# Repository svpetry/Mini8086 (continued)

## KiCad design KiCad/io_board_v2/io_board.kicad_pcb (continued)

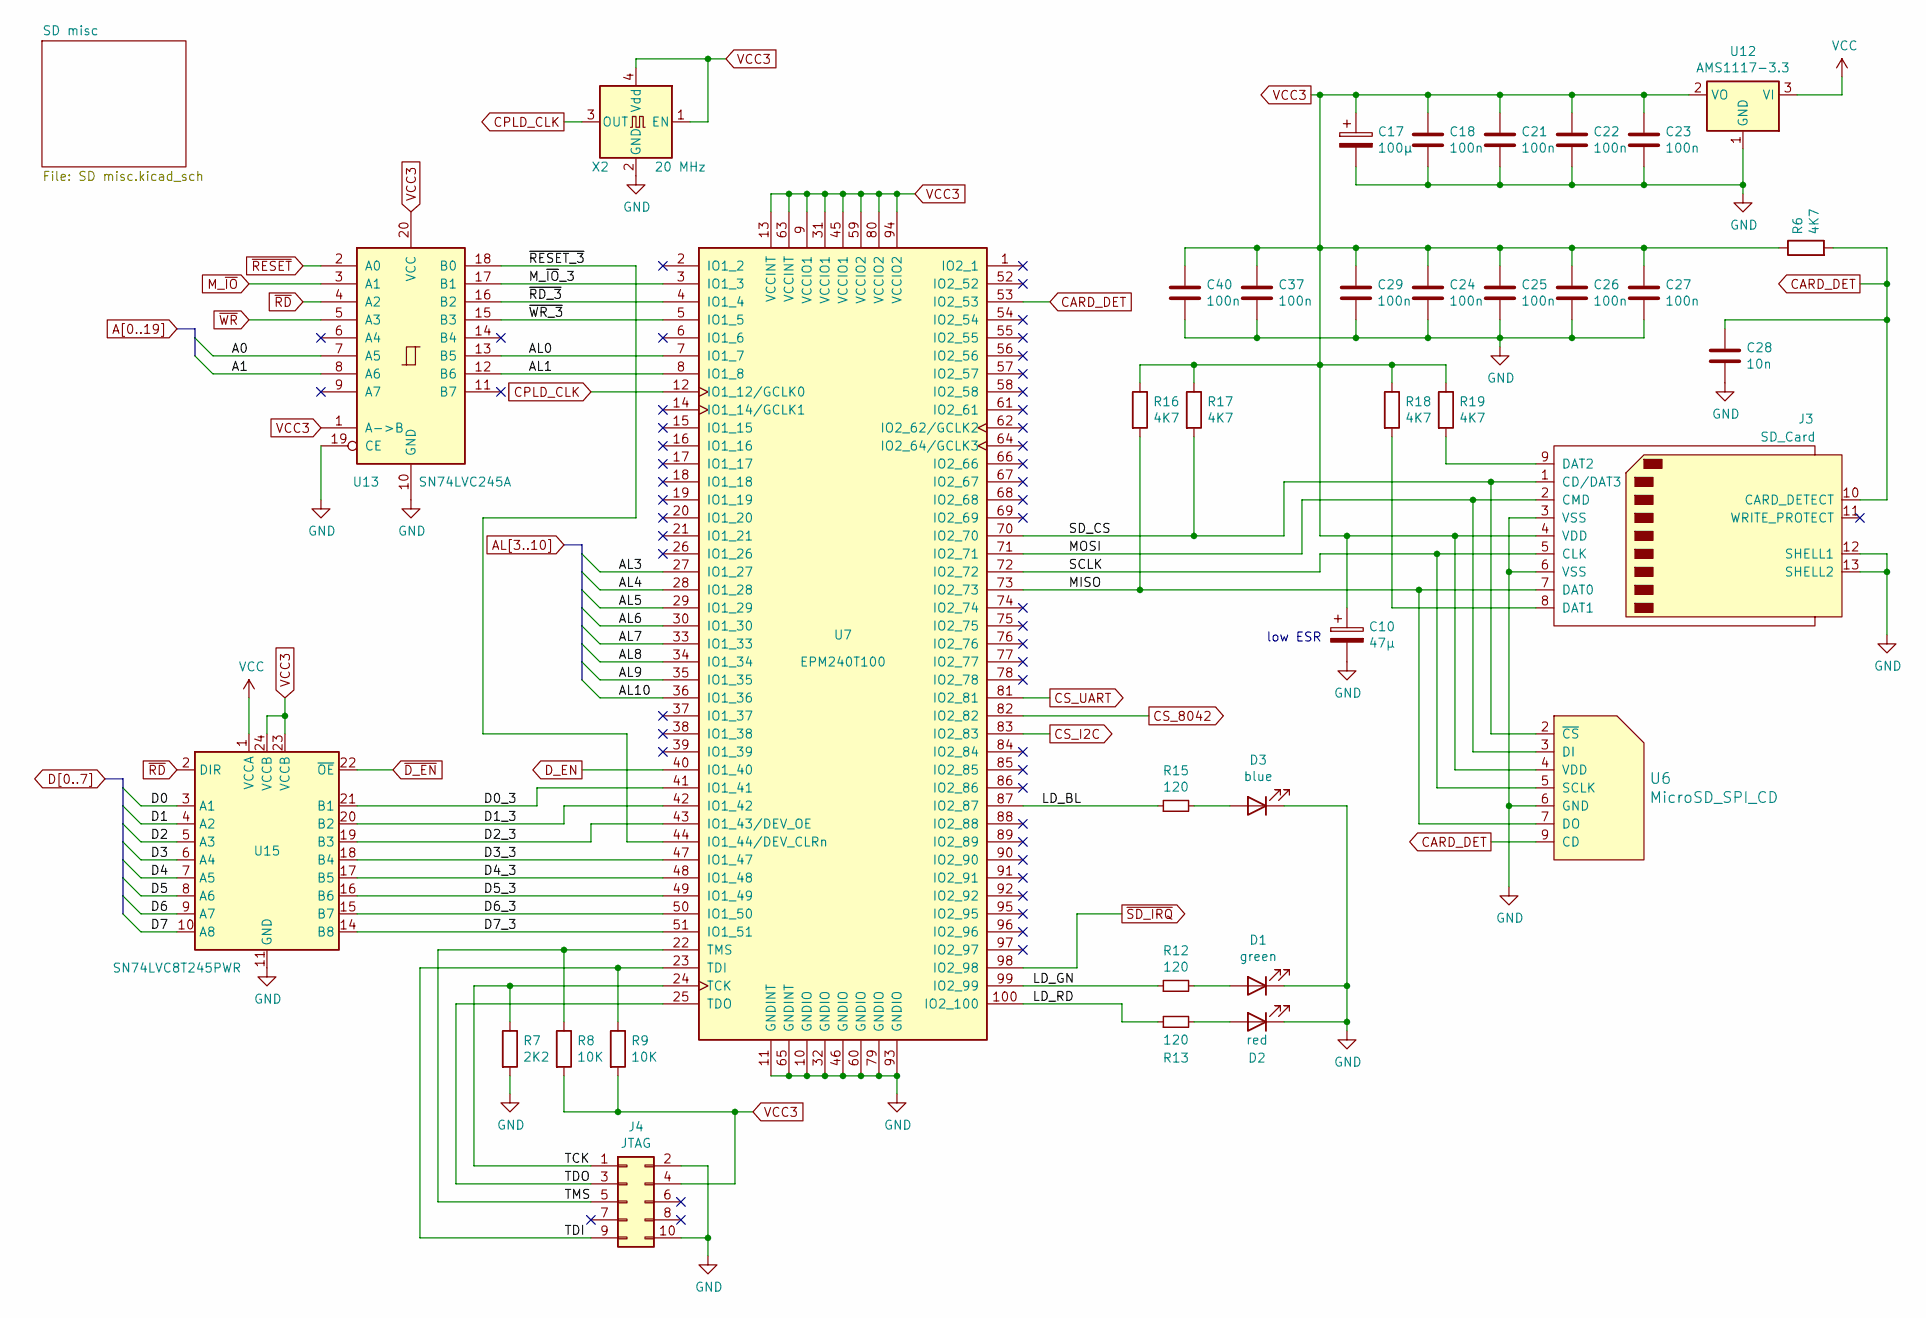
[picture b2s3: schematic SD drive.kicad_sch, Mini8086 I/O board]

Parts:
C10: 47µ; CP_Elec_5x5.4
C17: 100µ; CP_Elec_5x5.4
C18, C22, C24, C25, C26, C29, C37, C40: 100n; C_1206_3216Metric
C21, C23, C27: 100n; C_0805_2012Metric
C28: 10n; C_1206_3216Metric
D1: green; LED_1206_3216Metric
D2: red; LED_1206_3216Metric
D3: blue; LED_1206_3216Metric
J3: SD_Card; SD_TE_2041021
J4: JTAG; IDC-Header_2x05_P2.54mm_Vertical
R6, R16, R17, R18, R19: 4K7; R_1206_3216Metric
R7: 2K2; R_1206_3216Metric
R8, R9: 10K; R_1206_3216Metric
R12, R13, R15: 120; R_1206_3216Metric
U6: MicroSD_SPI_CD; GCT-MEM2055-00-190-01-A
U7: EPM240T100; LQFP-100_14x14mm_P0.5mm
U12: AMS1117-3.3; SOT-223-3_TabPin2
U13: SN74LVC245A; TSSOP-20_4.4x6.5mm_P0.65mm
U15: SN74LVC8T245PWR; TSSOP-24_4.4x7.8mm_P0.65mm
X2: 20 MHz; Oscillator_SMD_Abracon_ASV-4Pin_7.0x5.1mm

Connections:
/SD drive/AL0: U7.7 (IO1_7), U13.13 (B5)
/SD drive/AL1: U7.8 (IO1_8), U13.12 (B6)
/SD drive/D0_3: U7.41 (IO1_41), U15.21 (B1)
/SD drive/D1_3: U7.42 (IO1_42), U15.20 (B2)
/SD drive/D2_3: U7.43 (IO1_43/DEV_OE), U15.19 (B3)
/SD drive/D3_3: U7.47 (IO1_47), U15.18 (B4)
/SD drive/D4_3: U7.48 (IO1_48), U15.17 (B5)
/SD drive/D5_3: U7.49 (IO1_49), U15.16 (B6)
/SD drive/D6_3: U7.50 (IO1_50), U15.15 (B7)
/SD drive/D7_3: U7.51 (IO1_51), U15.14 (B8)
/SD drive/LD_BL: R15.1, U7.87 (IO2_87)
/SD drive/LD_GN: R12.1, U7.99 (IO2_99)
/SD drive/LD_RD: R13.1, U7.100 (IO2_100)
/SD drive/MISO: J3.7 (DAT0), R16.2, U6.7 (DO), U7.73 (IO2_73)
/SD drive/MOSI: J3.2 (CMD), U6.3 (DI), U7.71 (IO2_71)
/SD drive/M_~IO_3: U7.3 (IO1_3), U13.17 (B1)
/SD drive/SCLK: J3.5 (CLK), U6.5 (SCLK), U7.72 (IO2_72)
/SD drive/SD_CS: J3.1 (CD/DAT3), R17.2, U6.2 (~CS), U7.70 (IO2_70)
/SD drive/TCK: J4.1, R7.1, U7.24 (TCK)
/SD drive/TDI: J4.9, R9.1, U7.23 (TDI)
/SD drive/TDO: J4.3, U7.25 (TDO)
/SD drive/TMS: J4.5, R8.1, U7.22 (TMS)
/SD drive/~RD_3: U7.4 (IO1_4), U13.16 (B2)
/SD drive/~RESET_3: U7.44 (IO1_44/DEV_CLRn), U13.18 (B0)
/SD drive/~WR_3: U7.5 (IO1_5), U13.15 (B3)
A0: U13.7 (A5); also elsewhere on the board
A1: U13.8 (A6); also elsewhere on the board
AL3: U7.27 (IO1_27); also elsewhere on the board
AL4: U7.28 (IO1_28); also elsewhere on the board
AL5: U7.29 (IO1_29); also elsewhere on the board
AL6: U7.30 (IO1_30); also elsewhere on the board
AL7: U7.33 (IO1_33); also elsewhere on the board
AL8: U7.34 (IO1_34); also elsewhere on the board
AL9: U7.35 (IO1_35); also elsewhere on the board
AL10: U7.36 (IO1_36); also elsewhere on the board
CARD_DET: C28.1, J3.10 (CARD_DETECT), R6.2, U6.9 (CD), U7.53 (IO2_53)
CPLD_CLK: U7.12 (IO1_12/GCLK0), X2.3 (OUT)
CS_8042: U7.82 (IO2_82); also elsewhere on the board
CS_I2C: U7.83 (IO2_83); also elsewhere on the board
CS_UART: U7.81 (IO2_81); also elsewhere on the board
D0: U15.3 (A1); also elsewhere on the board
D1: U15.4 (A2); also elsewhere on the board
D2: U15.5 (A3); also elsewhere on the board
D3: U15.6 (A4); also elsewhere on the board
D4: U15.7 (A5); also elsewhere on the board
D5: U15.8 (A6); also elsewhere on the board
D6: U15.9 (A7); also elsewhere on the board
D7: U15.10 (A8); also elsewhere on the board
D_EN: U7.40 (IO1_40); also elsewhere on the board
GND: C10.2, C17.2, C18.2, C21.2, C22.2, C23.2, C24.2, C25.2, C26.2, C27.2, C28.2, C29.2, C37.2, C40.2, D1.1 (K), D2.1 (K), D3.1 (K), J3.3 (VSS), J3.6 (VSS), J3.12 (SHELL1), J3.13 (SHELL2), J4.2, J4.10, R7.2, U6.6 (GND), U7.10 (GNDIO), U7.11 (GNDINT), U7.32 (GNDIO), U7.46 (GNDIO), U7.60 (GNDIO), U7.65 (GNDINT), U7.79 (GNDIO), U7.93 (GNDIO), U12.1 (GND), U13.10 (GND), U13.19 (CE), U15.11 (GND), U15.12 (GND), U15.13 (GND), X2.2 (GND); also elsewhere on the board
M_~IO: U13.3 (A1); also elsewhere on the board
unnamed: D1.2 (A), R12.2
unnamed: D2.2 (A), R13.2
unnamed: D3.2 (A), R15.2
unnamed: J3.8 (DAT1), R18.2
unnamed: J3.9 (DAT2), R19.2
VCC: U12.3 (VI), U15.1 (VCCA); also elsewhere on the board
VCC3: C10.1, C17.1, C18.1, C21.1, C22.1, C23.1, C24.1, C25.1, C26.1, C27.1, C29.1, C37.1, C40.1, J3.4 (VDD), J4.4, R6.1, R8.2, R9.2, R16.1, R17.1, R18.1, R19.1, U6.4 (VDD), U7.9 (VCCIO1), U7.13 (VCCINT), U7.31 (VCCIO1), U7.45 (VCCIO1), U7.59 (VCCIO2), U7.63 (VCCINT), U7.80 (VCCIO2), U7.94 (VCCIO2), U12.2 (VO), U13.1 (A->B), U13.20 (VCC), U15.23 (VCCB), U15.24 (VCCB), X2.1 (EN), X2.4 (Vdd); also elsewhere on the board
~D_EN: U15.22 (~OE); also elsewhere on the board
~RD: U13.4 (A2), U15.2 (DIR); also elsewhere on the board
~RESET: U13.2 (A0); also elsewhere on the board
~SD_IRQ: U7.98 (IO2_98); also elsewhere on the board
~WR: U13.5 (A3); also elsewhere on the board

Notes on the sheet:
low ESR

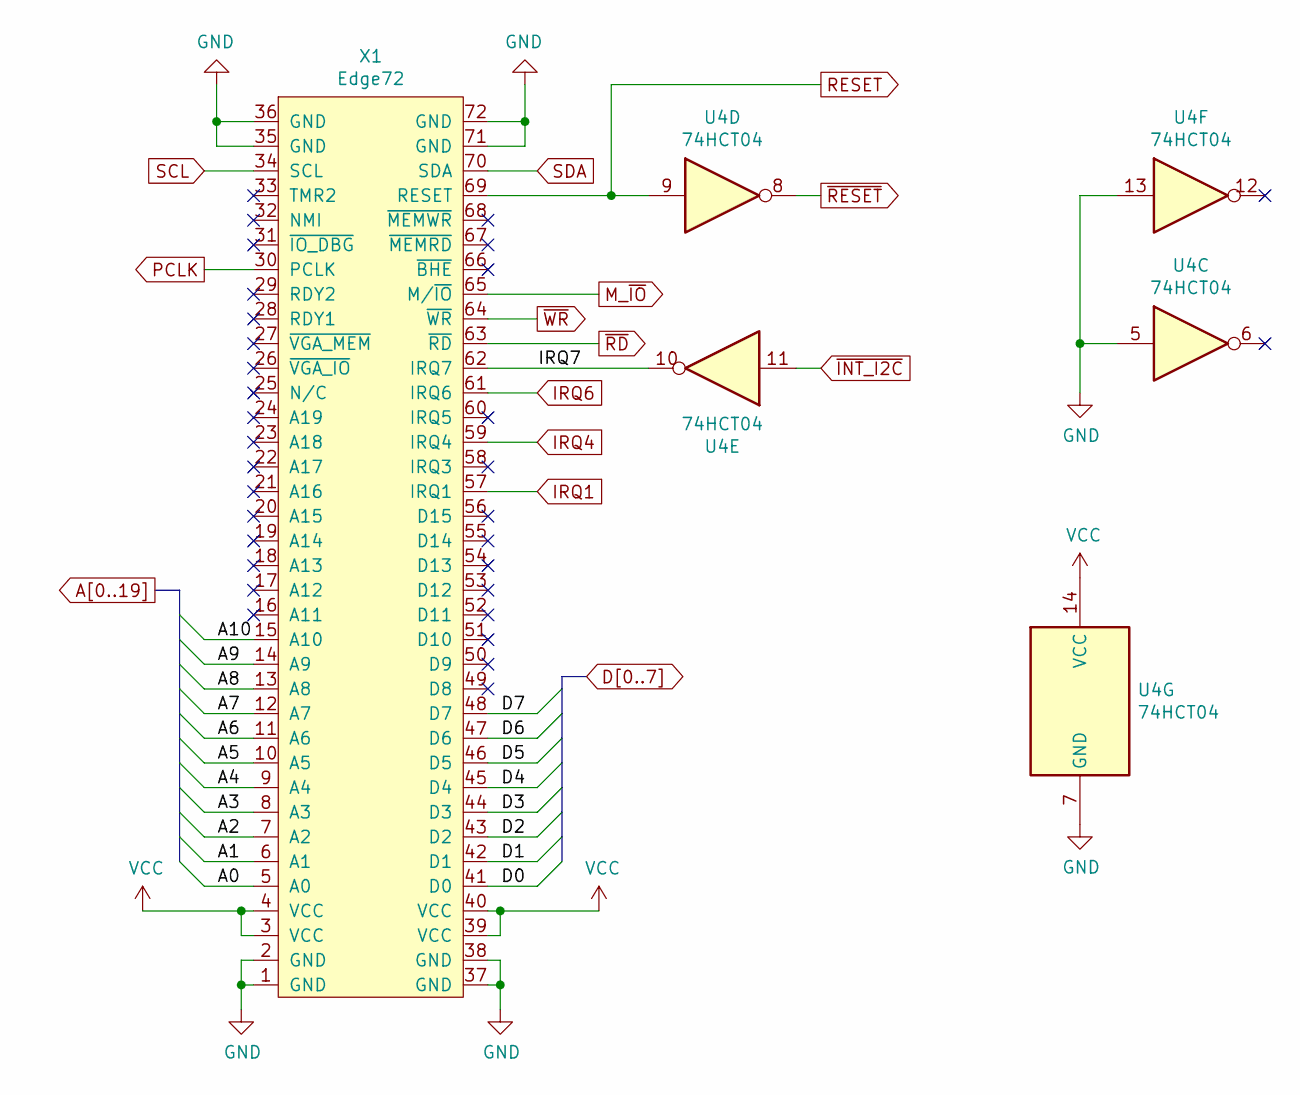
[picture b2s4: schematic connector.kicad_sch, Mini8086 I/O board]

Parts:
U4: 74HCT04; SOIC-14_3.9x8.7mm_P1.27mm
X1: Edge72; BUS_72

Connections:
/connector/IRQ7: U4.10, X1.62 (IRQ7)
A0: X1.5 (A0); also elsewhere on the board
A1: X1.6 (A1); also elsewhere on the board
A2: X1.7 (A2); also elsewhere on the board
A3: X1.8 (A3); also elsewhere on the board
A4: X1.9 (A4); also elsewhere on the board
A5: X1.10 (A5); also elsewhere on the board
A6: X1.11 (A6); also elsewhere on the board
A7: X1.12 (A7); also elsewhere on the board
A8: X1.13 (A8); also elsewhere on the board
A9: X1.14 (A9); also elsewhere on the board
A10: X1.15 (A10); also elsewhere on the board
D0: X1.41 (D0); also elsewhere on the board
D1: X1.42 (D1); also elsewhere on the board
D2: X1.43 (D2); also elsewhere on the board
D3: X1.44 (D3); also elsewhere on the board
D4: X1.45 (D4); also elsewhere on the board
D5: X1.46 (D5); also elsewhere on the board
D6: X1.47 (D6); also elsewhere on the board
D7: X1.48 (D7); also elsewhere on the board
GND: U4.5, U4.7 (GND), U4.13, X1.1 (GND), X1.2 (GND), X1.35 (GND), X1.36 (GND), X1.37 (GND), X1.38 (GND), X1.71 (GND), X1.72 (GND); also elsewhere on the board
IRQ1: X1.57 (IRQ1); also elsewhere on the board
IRQ4: X1.59 (IRQ4); also elsewhere on the board
IRQ6: X1.61 (IRQ6); also elsewhere on the board
M_~IO: X1.65 (M/~IO); also elsewhere on the board
PCLK: X1.30 (PCLK); also elsewhere on the board
RESET: U4.9, X1.69 (RESET); also elsewhere on the board
SCL: X1.34 (SCL); also elsewhere on the board
SDA: X1.70 (SDA); also elsewhere on the board
VCC: U4.14 (VCC), X1.3 (VCC), X1.4 (VCC), X1.39 (VCC), X1.40 (VCC); also elsewhere on the board
~INT_I2C: U4.11; also elsewhere on the board
~RD: X1.63 (~RD); also elsewhere on the board
~RESET: U4.8; also elsewhere on the board
~WR: X1.64 (~WR); also elsewhere on the board

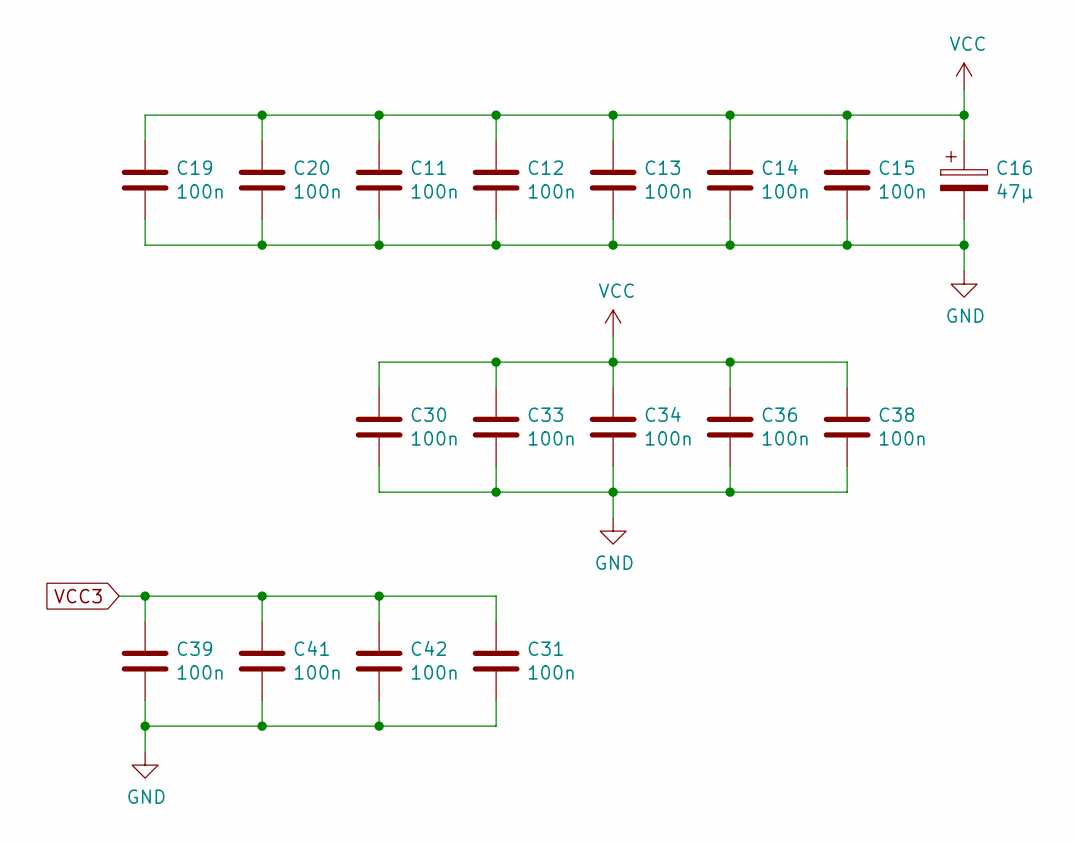
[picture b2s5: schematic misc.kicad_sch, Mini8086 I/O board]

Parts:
C11, C12, C13, C14, C15, C19, C20, C30, C33, C34, C36, C38, C39, C41, C42: 100n; C_1206_3216Metric
C16: 47µ; CP_Radial_D5.0mm_P2.00mm
C31: 100n; C_0805_2012Metric

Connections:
GND: C11.2, C12.2, C13.2, C14.2, C15.2, C16.2, C19.2, C20.2, C30.2, C31.2, C33.2, C34.2, C36.2, C38.2, C39.2, C41.2, C42.2; also elsewhere on the board
VCC: C11.1, C12.1, C13.1, C14.1, C15.1, C16.1, C19.1, C20.1, C30.1, C33.1, C34.1, C36.1, C38.1; also elsewhere on the board
VCC3: C31.1, C39.1, C41.1, C42.1; also elsewhere on the board

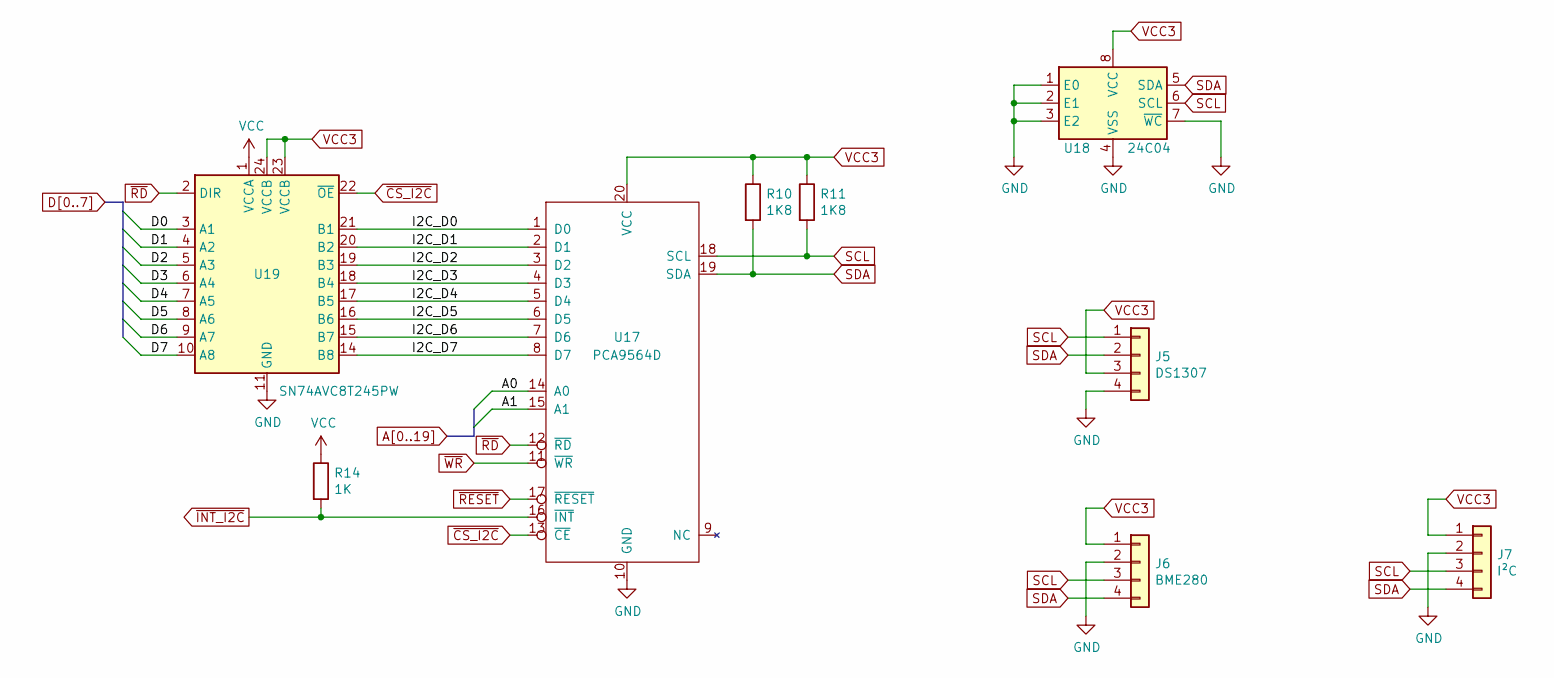
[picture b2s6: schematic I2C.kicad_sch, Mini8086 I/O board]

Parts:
J5: DS1307; PinHeader_1x04_P2.54mm_Vertical
J6: BME280; PinHeader_1x04_P2.54mm_Vertical
J7: I²C; PinHeader_1x04_P2.54mm_Vertical
R10, R11: 1K8; R_1206_3216Metric
R14: 1K; R_1206_3216Metric
U17: PCA9564D; SOIC-20W_7.5x12.8mm_P1.27mm
U18: 24C04; SOIC-8_3.9x4.9mm_P1.27mm
U19: SN74AVC8T245PW; TSSOP-24_4.4x7.8mm_P0.65mm

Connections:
/I2C/I2C_D0: U17.1 (D0), U19.21 (B1)
/I2C/I2C_D1: U17.2 (D1), U19.20 (B2)
/I2C/I2C_D2: U17.3 (D2), U19.19 (B3)
/I2C/I2C_D3: U17.4 (D3), U19.18 (B4)
/I2C/I2C_D4: U17.5 (D4), U19.17 (B5)
/I2C/I2C_D5: U17.6 (D5), U19.16 (B6)
/I2C/I2C_D6: U17.7 (D6), U19.15 (B7)
/I2C/I2C_D7: U17.8 (D7), U19.14 (B8)
A0: U17.14 (A0); also elsewhere on the board
A1: U17.15 (A1); also elsewhere on the board
D0: U19.3 (A1); also elsewhere on the board
D1: U19.4 (A2); also elsewhere on the board
D2: U19.5 (A3); also elsewhere on the board
D3: U19.6 (A4); also elsewhere on the board
D4: U19.7 (A5); also elsewhere on the board
D5: U19.8 (A6); also elsewhere on the board
D6: U19.9 (A7); also elsewhere on the board
D7: U19.10 (A8); also elsewhere on the board
GND: J5.4, J6.2, J7.2, U17.10 (GND), U18.1 (E0), U18.2 (E1), U18.3 (E2), U18.4 (VSS), U18.7 (~WC), U19.11 (GND), U19.12 (GND), U19.13 (GND); also elsewhere on the board
SCL: J5.1, J6.3, J7.3, R11.2, U17.18 (SCL), U18.6 (SCL); also elsewhere on the board
SDA: J5.2, J6.4, J7.4, R10.2, U17.19 (SDA), U18.5 (SDA); also elsewhere on the board
VCC: R14.1, U19.1 (VCCA); also elsewhere on the board
VCC3: J5.3, J6.1, J7.1, R10.1, R11.1, U17.20 (VCC), U18.8 (VCC), U19.23 (VCCB), U19.24 (VCCB); also elsewhere on the board
~CS_I2C: U17.13 (~CE), U19.22 (~OE); also elsewhere on the board
~INT_I2C: R14.2, U17.16 (~INT); also elsewhere on the board
~RD: U17.12 (~RD), U19.2 (DIR); also elsewhere on the board
~RESET: U17.17 (~RESET); also elsewhere on the board
~WR: U17.11 (~WR); also elsewhere on the board

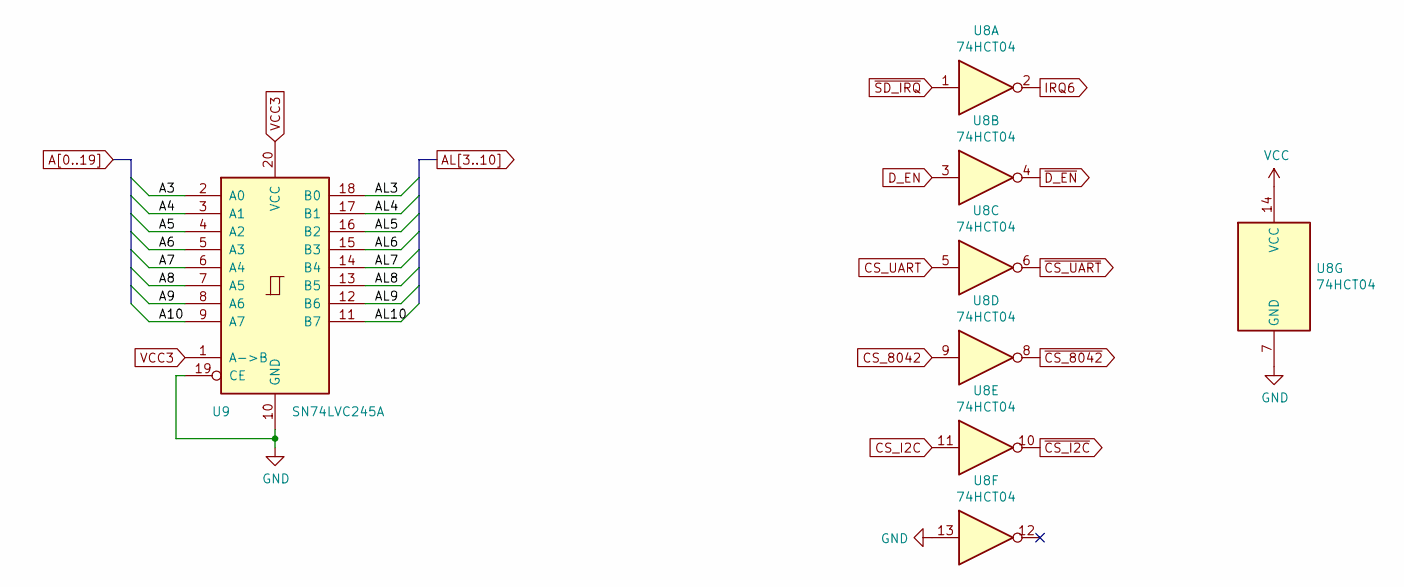
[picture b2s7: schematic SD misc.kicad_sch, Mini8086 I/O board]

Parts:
U8: 74HCT04; SOIC-14_3.9x8.7mm_P1.27mm
U9: SN74LVC245A; TSSOP-20_4.4x6.5mm_P0.65mm

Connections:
A3: U9.2 (A0); also elsewhere on the board
A4: U9.3 (A1); also elsewhere on the board
A5: U9.4 (A2); also elsewhere on the board
A6: U9.5 (A3); also elsewhere on the board
A7: U9.6 (A4); also elsewhere on the board
A8: U9.7 (A5); also elsewhere on the board
A9: U9.8 (A6); also elsewhere on the board
A10: U9.9 (A7); also elsewhere on the board
AL3: U9.18 (B0); also elsewhere on the board
AL4: U9.17 (B1); also elsewhere on the board
AL5: U9.16 (B2); also elsewhere on the board
AL6: U9.15 (B3); also elsewhere on the board
AL7: U9.14 (B4); also elsewhere on the board
AL8: U9.13 (B5); also elsewhere on the board
AL9: U9.12 (B6); also elsewhere on the board
AL10: U9.11 (B7); also elsewhere on the board
CS_8042: U8.9; also elsewhere on the board
CS_I2C: U8.11; also elsewhere on the board
CS_UART: U8.5; also elsewhere on the board
D_EN: U8.3; also elsewhere on the board
GND: U8.7 (GND), U8.13, U9.10 (GND), U9.19 (CE); also elsewhere on the board
IRQ6: U8.2; also elsewhere on the board
VCC: U8.14 (VCC); also elsewhere on the board
VCC3: U9.1 (A->B), U9.20 (VCC); also elsewhere on the board
~CS_8042: U8.8; also elsewhere on the board
~CS_I2C: U8.10; also elsewhere on the board
~CS_UART: U8.6; also elsewhere on the board
~D_EN: U8.4; also elsewhere on the board
~SD_IRQ: U8.1; also elsewhere on the board

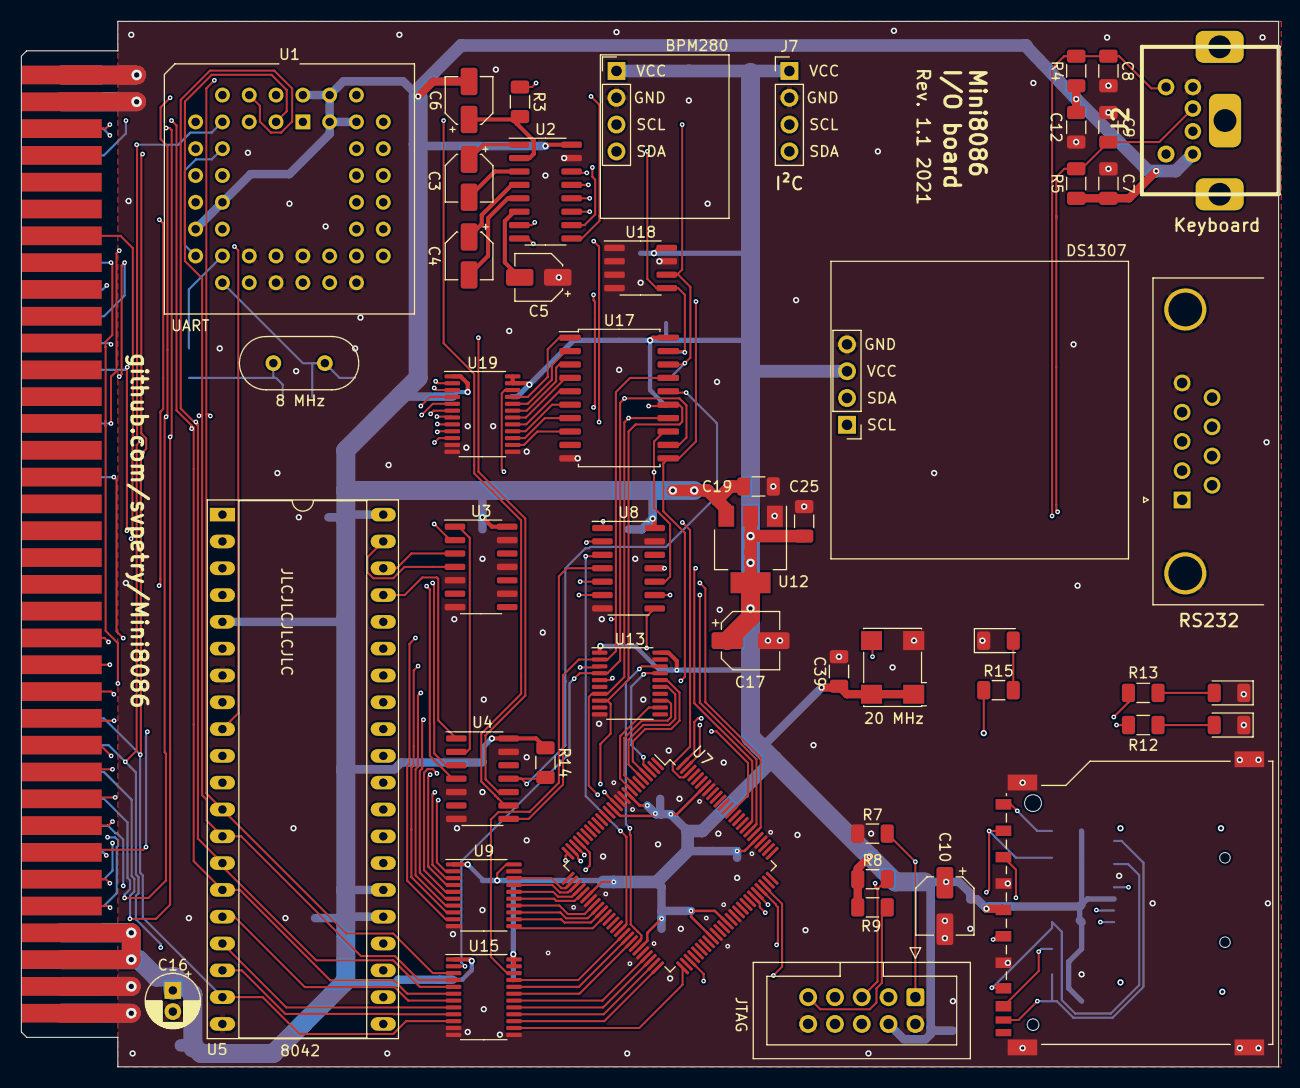
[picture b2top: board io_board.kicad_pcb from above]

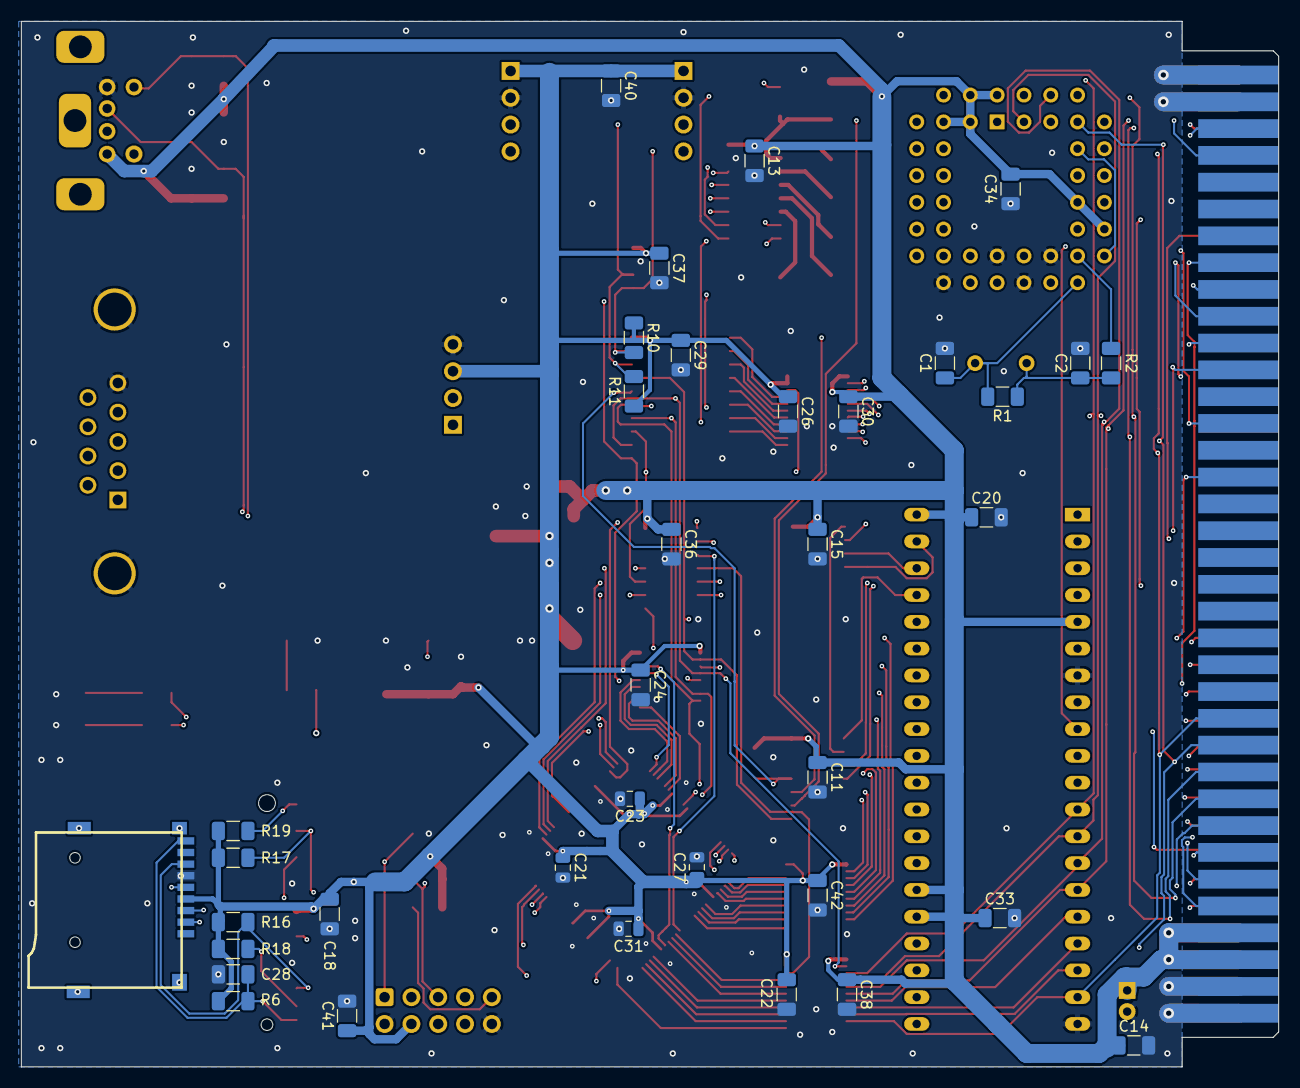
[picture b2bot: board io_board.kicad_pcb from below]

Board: 4 copper layers, 119.1 x 99.1 mm, 87 parts (36 on the bottom side), 117 nets.

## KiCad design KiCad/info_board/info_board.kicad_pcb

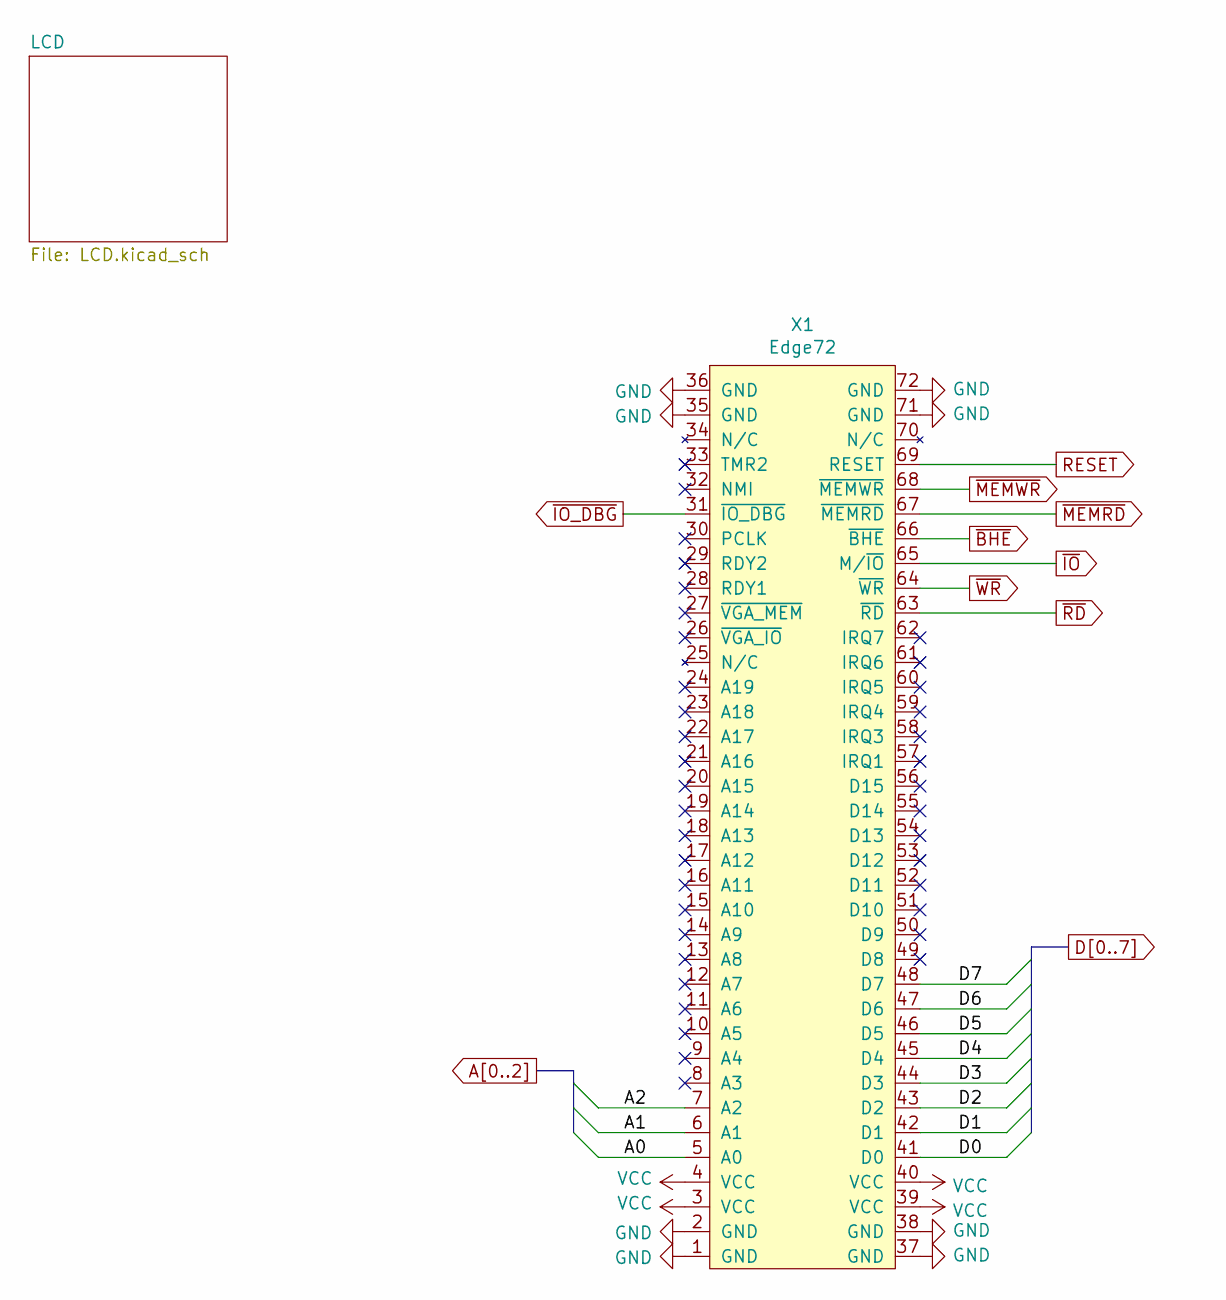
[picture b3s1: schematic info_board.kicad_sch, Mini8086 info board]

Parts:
X1: Edge72; BUS_72

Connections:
A0: X1.5 (A0); also elsewhere on the board
A1: X1.6 (A1); also elsewhere on the board
A2: X1.7 (A2); also elsewhere on the board
D0: X1.41 (D0); also elsewhere on the board
D1: X1.42 (D1); also elsewhere on the board
D2: X1.43 (D2); also elsewhere on the board
D3: X1.44 (D3); also elsewhere on the board
D4: X1.45 (D4); also elsewhere on the board
D5: X1.46 (D5); also elsewhere on the board
D6: X1.47 (D6); also elsewhere on the board
D7: X1.48 (D7); also elsewhere on the board
GND: X1.1 (GND), X1.2 (GND), X1.35 (GND), X1.36 (GND), X1.37 (GND), X1.38 (GND), X1.71 (GND), X1.72 (GND); also elsewhere on the board
RESET: X1.69 (RESET); also elsewhere on the board
VCC: X1.3 (VCC), X1.4 (VCC), X1.39 (VCC), X1.40 (VCC); also elsewhere on the board
~BHE: X1.66 (~BHE); also elsewhere on the board
~IO_DBG: X1.31 (~IO_DBG); also elsewhere on the board
~IO: X1.65 (M/~IO); also elsewhere on the board
~MEMRD: X1.67 (~MEMRD); also elsewhere on the board
~MEMWR: X1.68 (~MEMWR); also elsewhere on the board
~RD: X1.63 (~RD); also elsewhere on the board
~WR: X1.64 (~WR); also elsewhere on the board

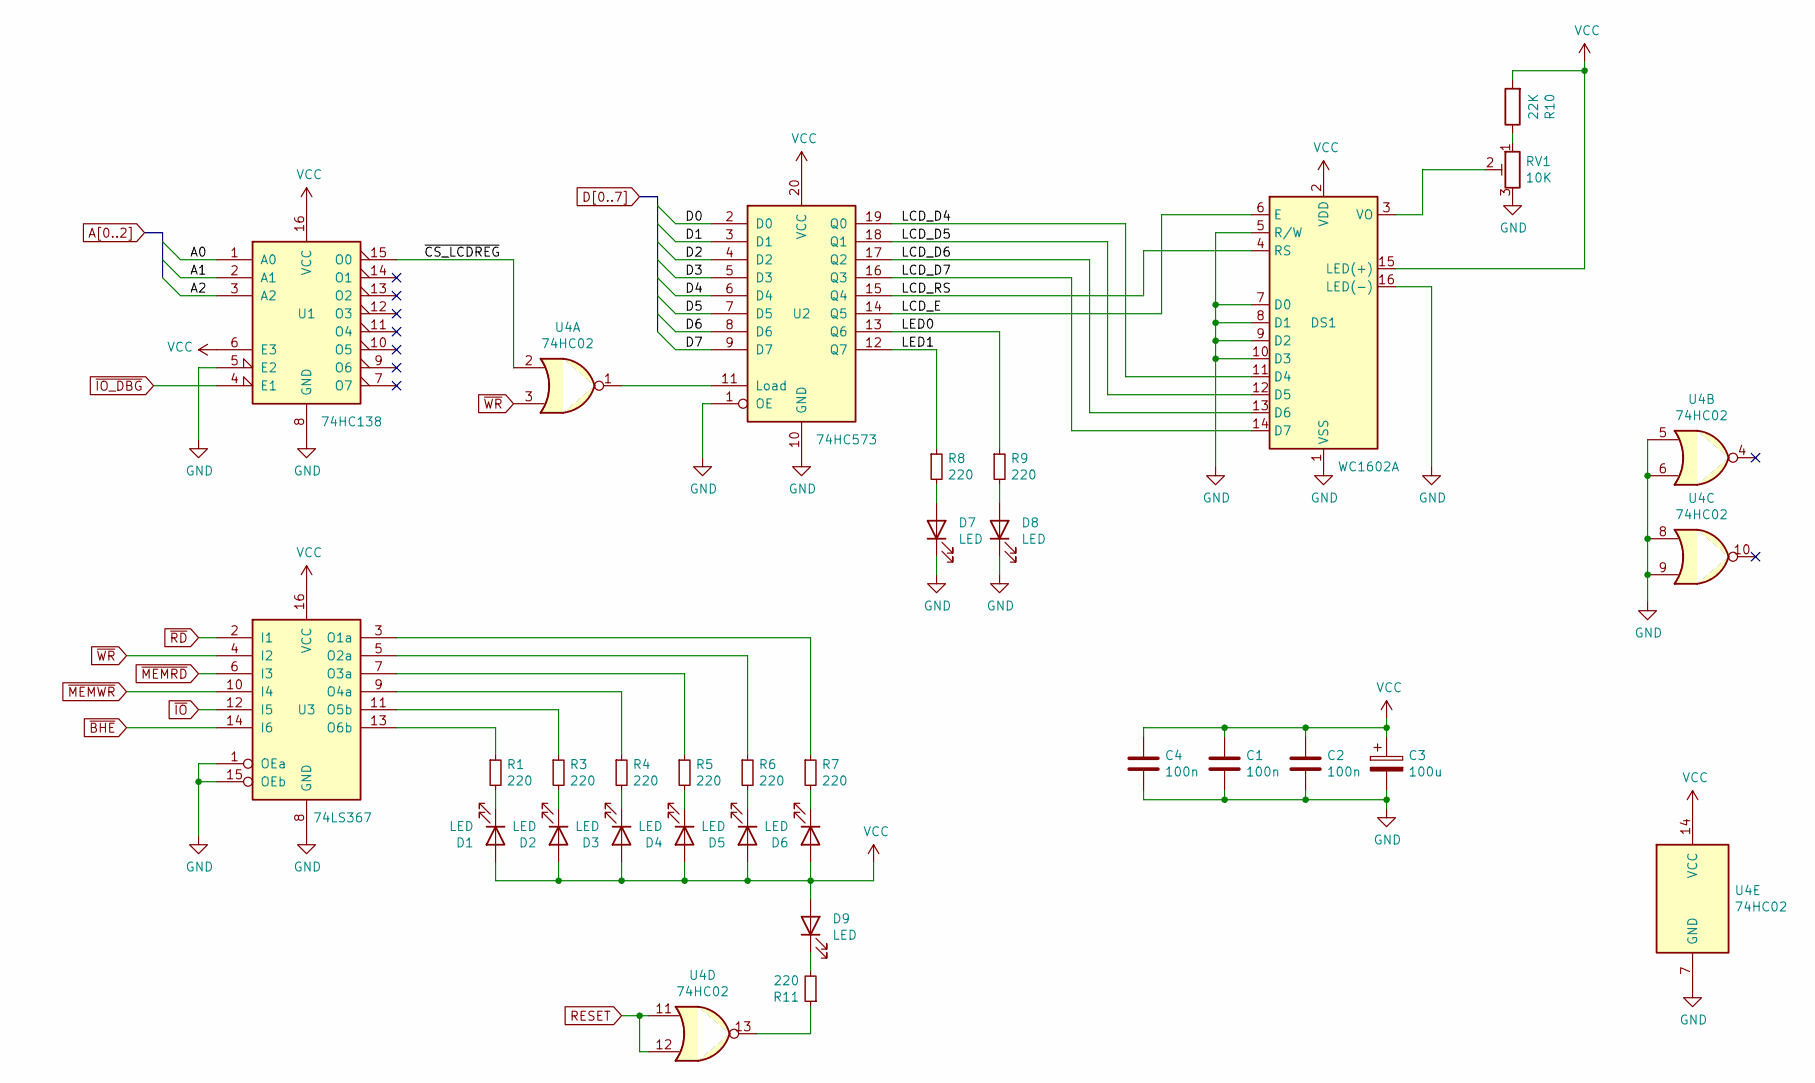
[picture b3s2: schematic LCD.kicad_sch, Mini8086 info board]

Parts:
C1, C2, C4: 100n; C_Disc_D4.3mm_W1.9mm_P5.00mm
C3: 100u; CP_Radial_D5.0mm_P2.50mm
D1, D2, D3, D4, D5, D6, D7, D8, D9: LED; LED_D5.0mm
DS1: WC1602A
R1, R3, R4, R5, R6, R7, R8, R9, R11: 220; R_Axial_DIN0207_L6.3mm_D2.5mm_P7.62mm_Horizontal
R10: 22K; R_Axial_DIN0207_L6.3mm_D2.5mm_P7.62mm_Horizontal
RV1: 10K; Potentiometer_Piher_PT-10-V05_Vertical
U1: 74HC138; DIP-16_W7.62mm_LongPads
U2: 74HC573; DIP-20_W7.62mm_LongPads
U3: 74LS367; DIP-16_W7.62mm_LongPads
U4: 74HC02; DIP-14_W7.62mm_LongPads

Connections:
/LCD/LCD_D4: DS1.11 (D4), U2.19 (Q0)
/LCD/LCD_D5: DS1.12 (D5), U2.18 (Q1)
/LCD/LCD_D6: DS1.13 (D6), U2.17 (Q2)
/LCD/LCD_D7: DS1.14 (D7), U2.16 (Q3)
/LCD/LCD_E: DS1.6 (E), U2.14 (Q5)
/LCD/LCD_RS: DS1.4 (RS), U2.15 (Q4)
/LCD/LED0: R9.1, U2.13 (Q6)
/LCD/LED1: R8.1, U2.12 (Q7)
/LCD/~CS_LCDREG: U1.15 (O0), U4.2
A0: U1.1 (A0); also elsewhere on the board
A1: U1.2 (A1); also elsewhere on the board
A2: U1.3 (A2); also elsewhere on the board
D0: U2.2 (D0); also elsewhere on the board
D1: U2.3 (D1); also elsewhere on the board
D2: U2.4 (D2); also elsewhere on the board
D3: U2.5 (D3); also elsewhere on the board
D4: U2.6 (D4); also elsewhere on the board
D5: U2.7 (D5); also elsewhere on the board
D6: U2.8 (D6); also elsewhere on the board
D7: U2.9 (D7); also elsewhere on the board
GND: C1.2, C2.2, C3.2, C4.2, D7.1 (K), D8.1 (K), DS1.1 (VSS), DS1.5 (R/W), DS1.7 (D0), DS1.8 (D1), DS1.9 (D2), DS1.10 (D3), DS1.16 (LED(-)), RV1.3, U1.5 (E2), U1.8 (GND), U2.1 (OE), U2.10 (GND), U3.1 (OEa), U3.8 (GND), U3.15 (OEb), U4.5, U4.6, U4.7 (GND), U4.8, U4.9; also elsewhere on the board
unnamed: D1.1 (K), R1.2
unnamed: D2.1 (K), R3.2
unnamed: D3.1 (K), R4.2
unnamed: D4.1 (K), R5.2
unnamed: D5.1 (K), R6.2
unnamed: D6.1 (K), R7.2
unnamed: D7.2 (A), R8.2
unnamed: D8.2 (A), R9.2
unnamed: D9.1 (K), R11.2
unnamed: DS1.3 (VO), RV1.2
unnamed: R10.1, RV1.1
unnamed: R11.1, U4.13
unnamed: U2.11 (Load), U4.1
unnamed: R7.1, U3.3 (O1a)
unnamed: R6.1, U3.5 (O2a)
unnamed: R5.1, U3.7 (O3a)
unnamed: R4.1, U3.9 (O4a)
unnamed: R3.1, U3.11 (O5b)
unnamed: R1.1, U3.13 (O6b)
RESET: U4.11, U4.12; also elsewhere on the board
VCC: C1.1, C2.1, C3.1, C4.1, D1.2 (A), D2.2 (A), D3.2 (A), D4.2 (A), D5.2 (A), D6.2 (A), D9.2 (A), DS1.2 (VDD), DS1.15 (LED(+)), R10.2, U1.6 (E3), U1.16 (VCC), U2.20 (VCC), U3.16 (VCC), U4.14 (VCC); also elsewhere on the board
~BHE: U3.14 (I6); also elsewhere on the board
~IO_DBG: U1.4 (E1); also elsewhere on the board
~IO: U3.12 (I5); also elsewhere on the board
~MEMRD: U3.6 (I3); also elsewhere on the board
~MEMWR: U3.10 (I4); also elsewhere on the board
~RD: U3.2 (I1); also elsewhere on the board
~WR: U3.4 (I2), U4.3; also elsewhere on the board
